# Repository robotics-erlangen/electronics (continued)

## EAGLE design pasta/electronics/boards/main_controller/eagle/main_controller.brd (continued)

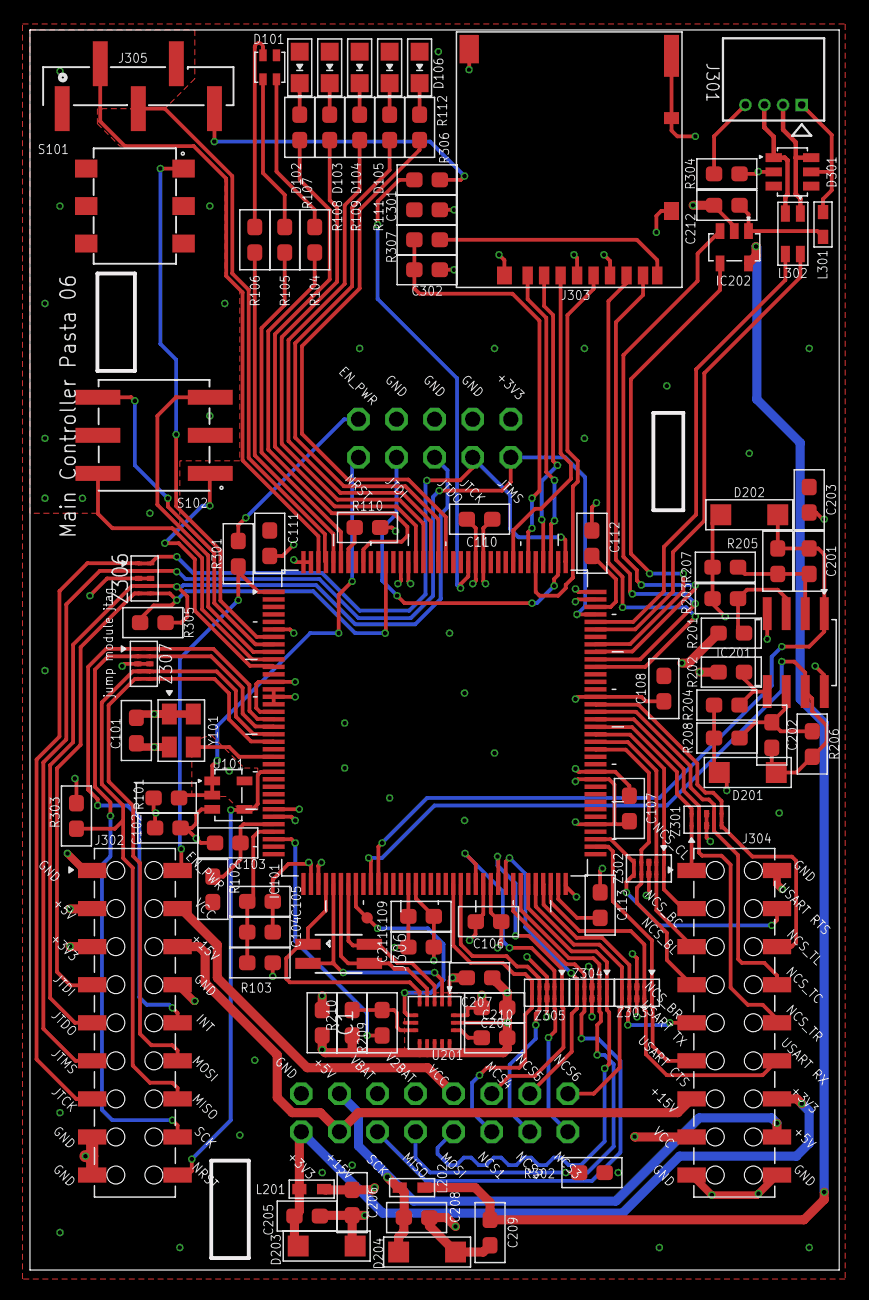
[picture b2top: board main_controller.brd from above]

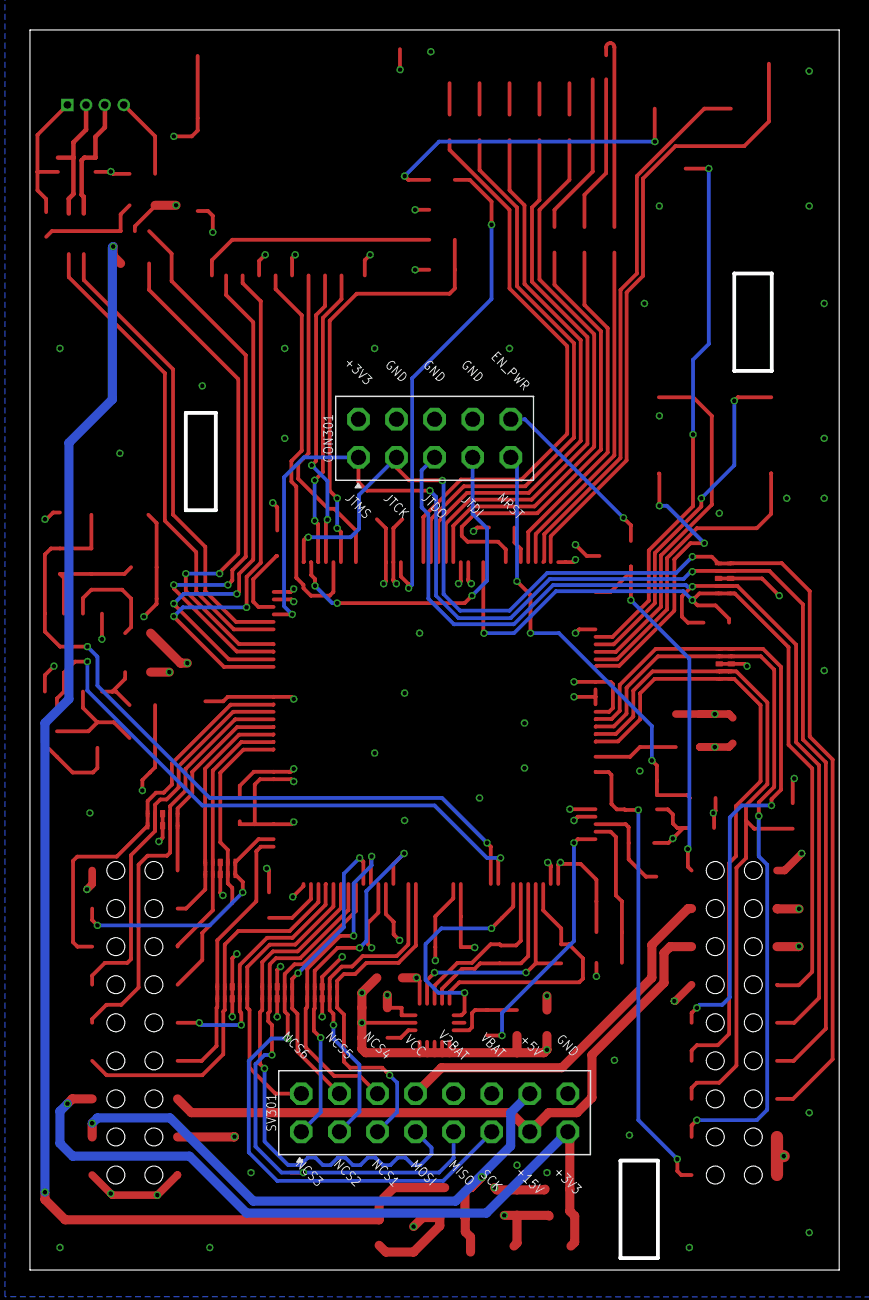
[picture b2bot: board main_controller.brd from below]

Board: 4 copper layers, 54.0 x 82.8 mm, 97 parts (2 on the bottom side), 104 nets.

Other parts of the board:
U$1: POWER_DISTRIBUTION_BOARD_TOP

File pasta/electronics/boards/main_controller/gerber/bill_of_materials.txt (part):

Stückliste exportiert aus D:/hardware/pasta/electronics/boards/main_controller/eagle/main_controller.sch am 04.07.2023 15:47

Part   Value             Device                     Package                  Description                                                                                                                          CAPACITANCE COPYRIGHT                                                DIELECTRIC FARNELL LINE1     LINE2    MF                          MOUSER               MPN              POPULARITY POWER RESISTANCE TOLERANCE VALUE             VOLTAGE WE-NUMBER              
301    TEST-POINT3       TEST-POINT3                PAD.03X.03                                                                                                                                                                                                                                                                                                                                                                                                                        
C1     100n ±10% 50V X7R C(100NF,50V,0603)          C0603                    Robotics Erlangen Capacitor Library                                                                                                  100n                                                                 X7R                100n ±10% 50V X7R  Würth Elektronik                                 885012206095                                 ±10%      100n ±10% 50V X7R 50V                            
C101   100n ±10% 50V X7R C(100NF,50V,0603)          C0603                    Robotics Erlangen Capacitor Library                                                                                                  100n                                                                 X7R                100n ±10% 50V X7R  Würth Elektronik                                 885012206095                                 ±10%      100n ±10% 50V X7R 50V                            
C102   100n ±10% 50V X7R C(100NF,50V,0603)          C0603                    Robotics Erlangen Capacitor Library                                                                                                  100n                                                                 X7R                100n ±10% 50V X7R  Würth Elektronik                                 885012206095                                 ±10%      100n ±10% 50V X7R 50V                            
C103   470n ±10% 25V X7R C(470NF,25V,0603)          C0603                    Robotics Erlangen Capacitor Library                                                                                                  470n                                                                 X7R                470n ±10% 25V X7R  Würth Elektronik                                 885012206075                                 ±10%      470n ±10% 25V X7R 25V                            
C104   1u ±10% 25V X7R   C(1.0UF,25V,0603)          C0603                    Robotics Erlangen Capacitor Library                                                                                                  1u                                                                   X7R                1u ±10%   25V X7R  Würth Elektronik                                 885012206076                                 ±10%      1u ±10% 25V X7R   25V                            
C105   100n ±10% 50V X7R C(100NF,50V,0603)          C0603                    Robotics Erlangen Capacitor Library                                                                                                  100n                                                                 X7R                100n ±10% 50V X7R  Würth Elektronik                                 885012206095                                 ±10%      100n ±10% 50V X7R 50V                            
C106   100n ±10% 50V X7R C(100NF,50V,0603)          C0603                    Robotics Erlangen Capacitor Library                                                                                                  100n                                                                 X7R                100n ±10% 50V X7R  Würth Elektronik                                 885012206095                                 ±10%      100n ±10% 50V X7R 50V                            
C107   100n ±10% 50V X7R C(100NF,50V,0603)          C0603                    Robotics Erlangen Capacitor Library                                                                                                  100n                                                                 X7R                100n ±10% 50V X7R  Würth Elektronik                                 885012206095                                 ±10%      100n ±10% 50V X7R 50V                            
C108   100n ±10% 50V X7R C(100NF,50V,0603)          C0603                    Robotics Erlangen Capacitor Library                                                                                                  100n                                                                 X7R                100n ±10% 50V X7R  Würth Elektronik                                 885012206095                                 ±10%      100n ±10% 50V X7R 50V                            
C109   100n ±10% 50V X7R C(100NF,50V,0603)          C0603                    Robotics Erlangen Capacitor Library                                                                                                  100n                                                                 X7R                100n ±10% 50V X7R  Würth Elektronik                                 885012206095                                 ±10%      100n ±10% 50V X7R 50V                            
C110   100n ±10% 50V X7R C(100NF,50V,0603)          C0603                    Robotics Erlangen Capacitor Library                                                                                                  100n                                                                 X7R                100n ±10% 50V X7R  Würth Elektronik                                 885012206095                                 ±10%      100n ±10% 50V X7R 50V                            
C111   4u7 ±20% 6V3 X5R  C(4.7UF,6.3V,0603)         C0603                    Robotics Erlangen Capacitor Library                                                                                                  4u7                                                                  X5R                4u7 ±20%  6V3 X5R  Würth Elektronik                                 885012106005                                 ±20%      4u7 ±20% 6V3 X5R  6V3                            
C112   2u2 ±20% 6V3 X5R  C(2.2UF,6.3V,0603)         C0603                    Robotics Erlangen Capacitor Library                                                                                                  2u2                                                                  X5R                2u2 ±20%  6V3 X5R  Würth Elektronik                                 885012106004                                 ±20%      2u2 ±20% 6V3 X5R  6V3                            
C113   2u2 ±20% 6V3 X5R  C(2.2UF,6.3V,0603)         C0603                    Robotics Erlangen Capacitor Library                                                                                                  2u2                                                                  X5R                2u2 ±20%  6V3 X5R  Würth Elektronik                                 885012106004                                 ±20%      2u2 ±20% 6V3 X5R  6V3                            
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
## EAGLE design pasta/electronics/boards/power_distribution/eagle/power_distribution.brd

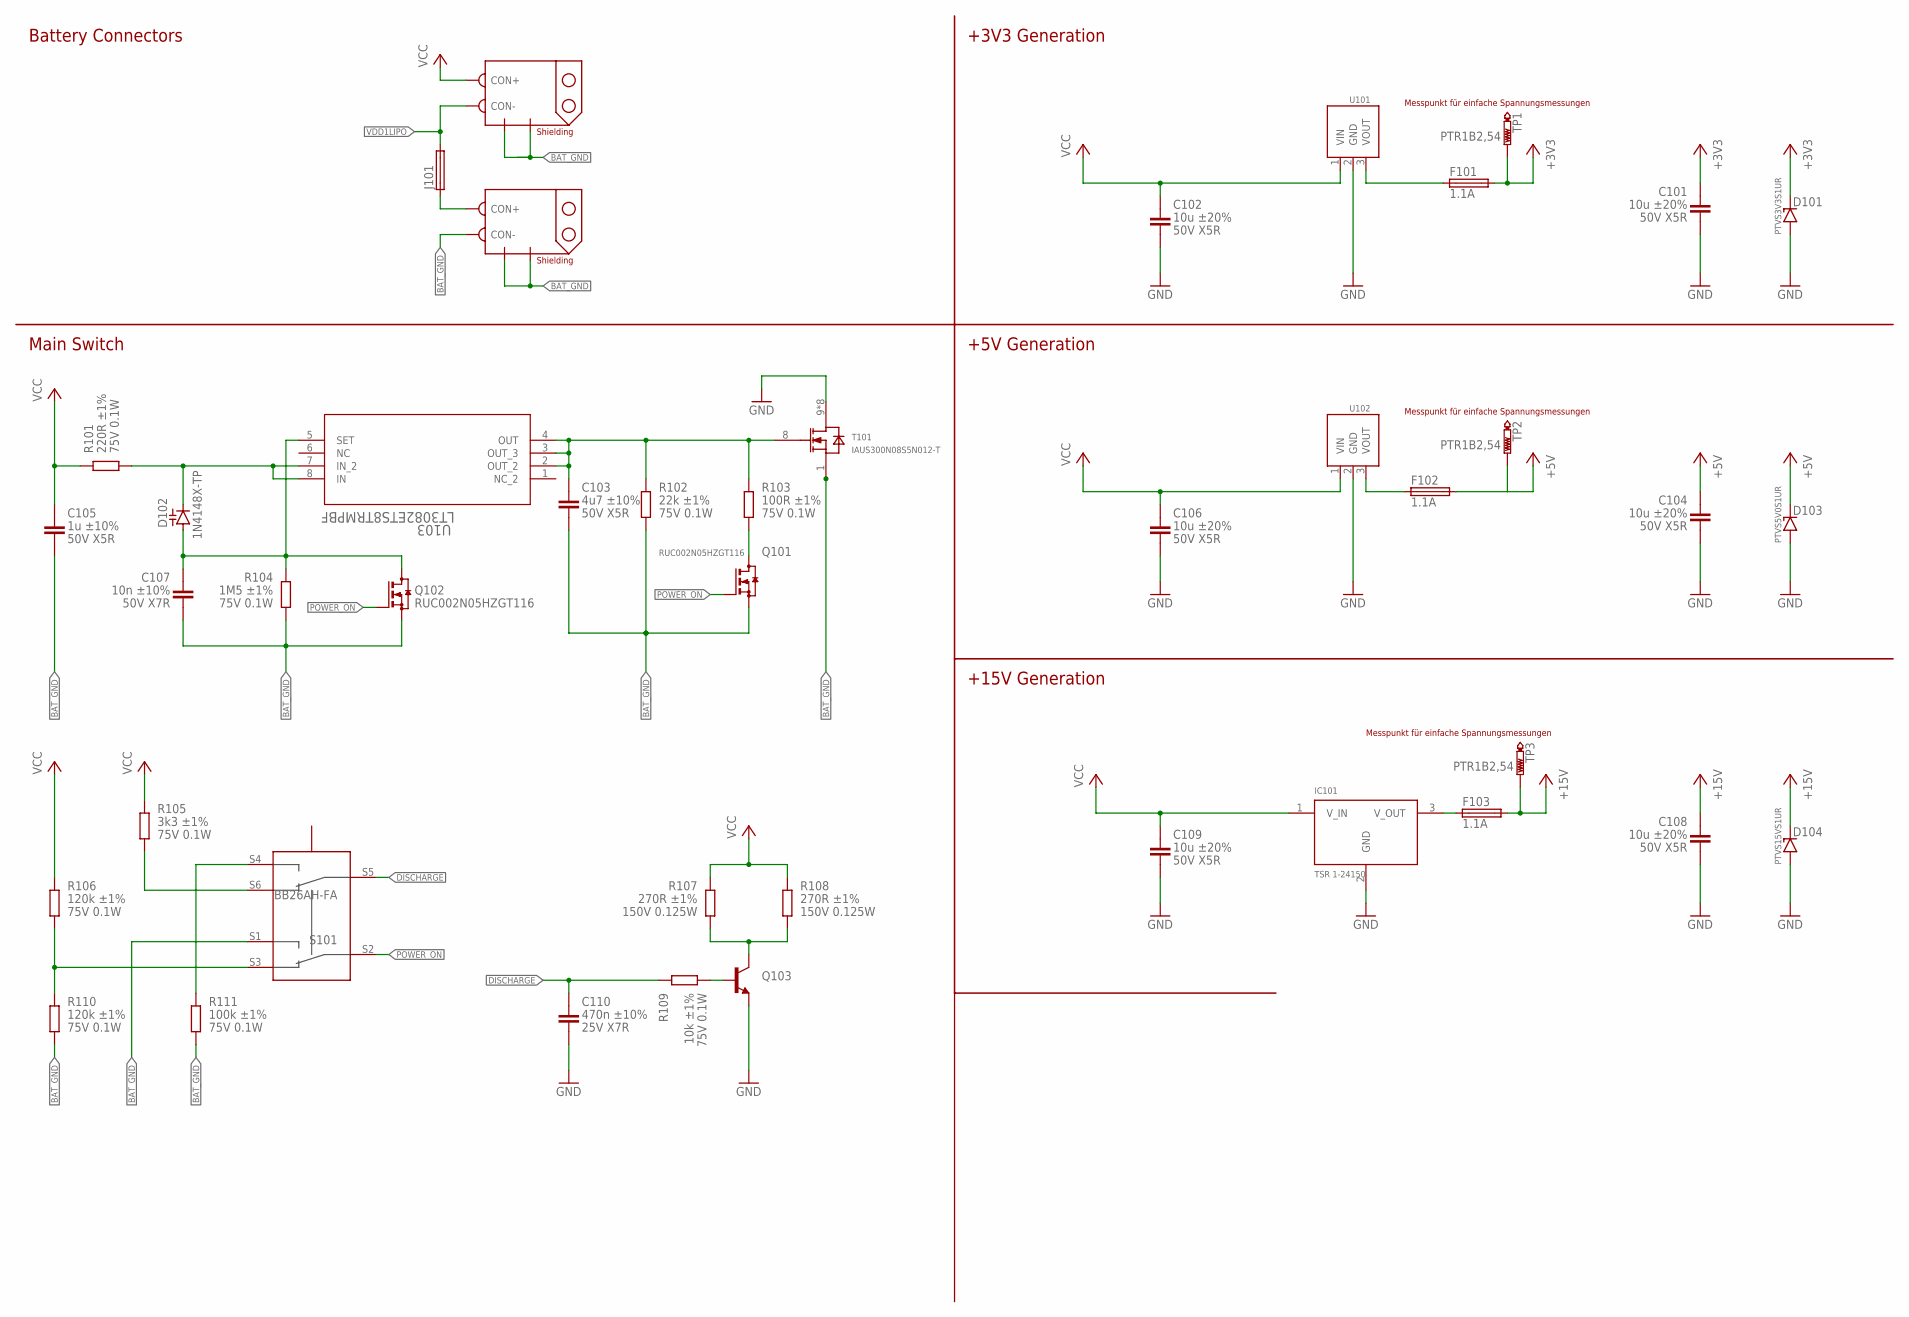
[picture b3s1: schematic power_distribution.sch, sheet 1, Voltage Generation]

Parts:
C101, C102, C104, C106, C108, C109: 10u ±20% 50V X5R; C1206
C103: 4u7 ±10% 50V X5R; C0805
C105: 1u ±10% 50V X5R; C0603
C107: 10n ±10% 50V X7R; C0603
C110: 470n ±10% 25V X7R; C0603
CON101, CON102: XT60PW; XT60PW-M
D101: PTVS3V3S1UR; SOD123
D102: 1N4148X-TP; SOD523
D103: PTVS5V0S1UR; SOD123
D104: PTVS15VS1UR; SOD123
F101, F102, F103: 1.1A; MF-NSMF-1
IC101: TSR 1-24150; TRACO_POWER_3_PIN
J101: 696107003002
Q101, Q102: RUC002N05HZGT116; SOT23
Q103: FJT44TF"; SOT223
R101: 220R ±1% 75V 0.1W; R0603
R102: 22k ±1% 75V 0.1W; R0603
R103: 100R ±1% 75V 0.1W; R0603
R104: 1M5 ±1% 75V 0.1W; R0603
R105: 3k3 ±1% 75V 0.1W; R0603
R106, R110: 120k ±1% 75V 0.1W; R0603
R107, R108: 270R ±1% 150V 0.125W; R0805
R109: 10k ±1% 75V 0.1W; R0603
R111: 100k ±1% 75V 0.1W; R0603
S101: BB26AH-FA; BB26AH
T101: IAUS300N08S5N012-T; SOIC120P1500X235-16N-1-V
TP1, TP2, TP3: PTR1B2,54; B2,54
U101: FDSM_SIP-3_173010342; FDSM-173XXXX42
U102: FDSM_SIP-3_173010542; FDSM-173XXXX42
U103: LT3082ETS8TRMPBF; TSOT-23_TS8

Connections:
+3V3: C101.1, D101.C (KATHODE), F101.2, TP1.TP; also elsewhere on the board
+5V: C104.1, D103.C (KATHODE), F102.2, TP2.TP; also elsewhere on the board
+15V: C108.1, D104.C (KATHODE), F103.2, TP3.TP; also elsewhere on the board
BAT_GND: C103.2, C105.2, C107.2, CON101.S1, CON101.S2, CON102.CON-, CON102.S1, CON102.S2, Q101.2 (S), Q102.2 (S), R102.1, R104.1, R110.1, R111.1, S101.S1 (2), T101.1 (SOURCE_1)
DISCHARGE: C110.1, R109.1, S101.S5 (4)
GND: C101.2, C102.2, C104.2, C106.2, C108.2, C109.2, C110.2, D101.A (ANODE), D103.A (ANODE), D104.A (ANODE), IC101.2 (GND), Q103.3 (E), T101.9 (DRAIN), T101.10 (DRAIN), T101.11 (DRAIN), T101.12 (DRAIN), T101.13 (DRAIN), T101.14 (DRAIN), T101.15 (DRAIN), T101.16 (DRAIN), U101.2 (GND), U102.2 (GND); also elsewhere on the board
unnamed: CON102.CON+, J101.1
unnamed: C103.1, R102.2, R103.2, T101.8 (GATE), U103.2 (OUT_2), U103.3 (OUT_3), U103.4 (OUT)
unnamed: Q101.3 (D), R103.1
unnamed: R106.1, R110.2, S101.S3 (3)
unnamed: F101.1, U101.3 (VOUT)
unnamed: R105.1, S101.S6 (6)
unnamed: F103.1, IC101.3 (V_OUT)
unnamed: R111.2, S101.S4 (5)
unnamed: F102.1, U102.3 (VOUT)
unnamed: Q103.2 (C), Q103.4 (C), R107.1, R108.1
unnamed: Q103.1 (B), R109.2
unnamed: D102.C, R101.1, U103.7 (IN_2), U103.8 (IN)
POWER_ON: Q101.1 (G), Q102.1 (G), S101.S2 (1)
SETPIN: C107.1, D102.A, Q102.3 (D), R104.2, U103.5 (SET)
VCC: C102.1, C105.1, C106.1, C109.1, CON101.CON+, IC101.1 (V_IN), R101.2, R105.2, R106.2, R107.2, R108.2, U101.1 (VIN), U102.1 (VIN); also elsewhere on the board
VDD1LIPO: CON101.CON-, J101.2; also elsewhere on the board

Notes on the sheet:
+3V3 Generation
+5V Generation
+15V Generation
Main Switch
Battery Connectors
Messpunkt für einfache Spannungsmessungen

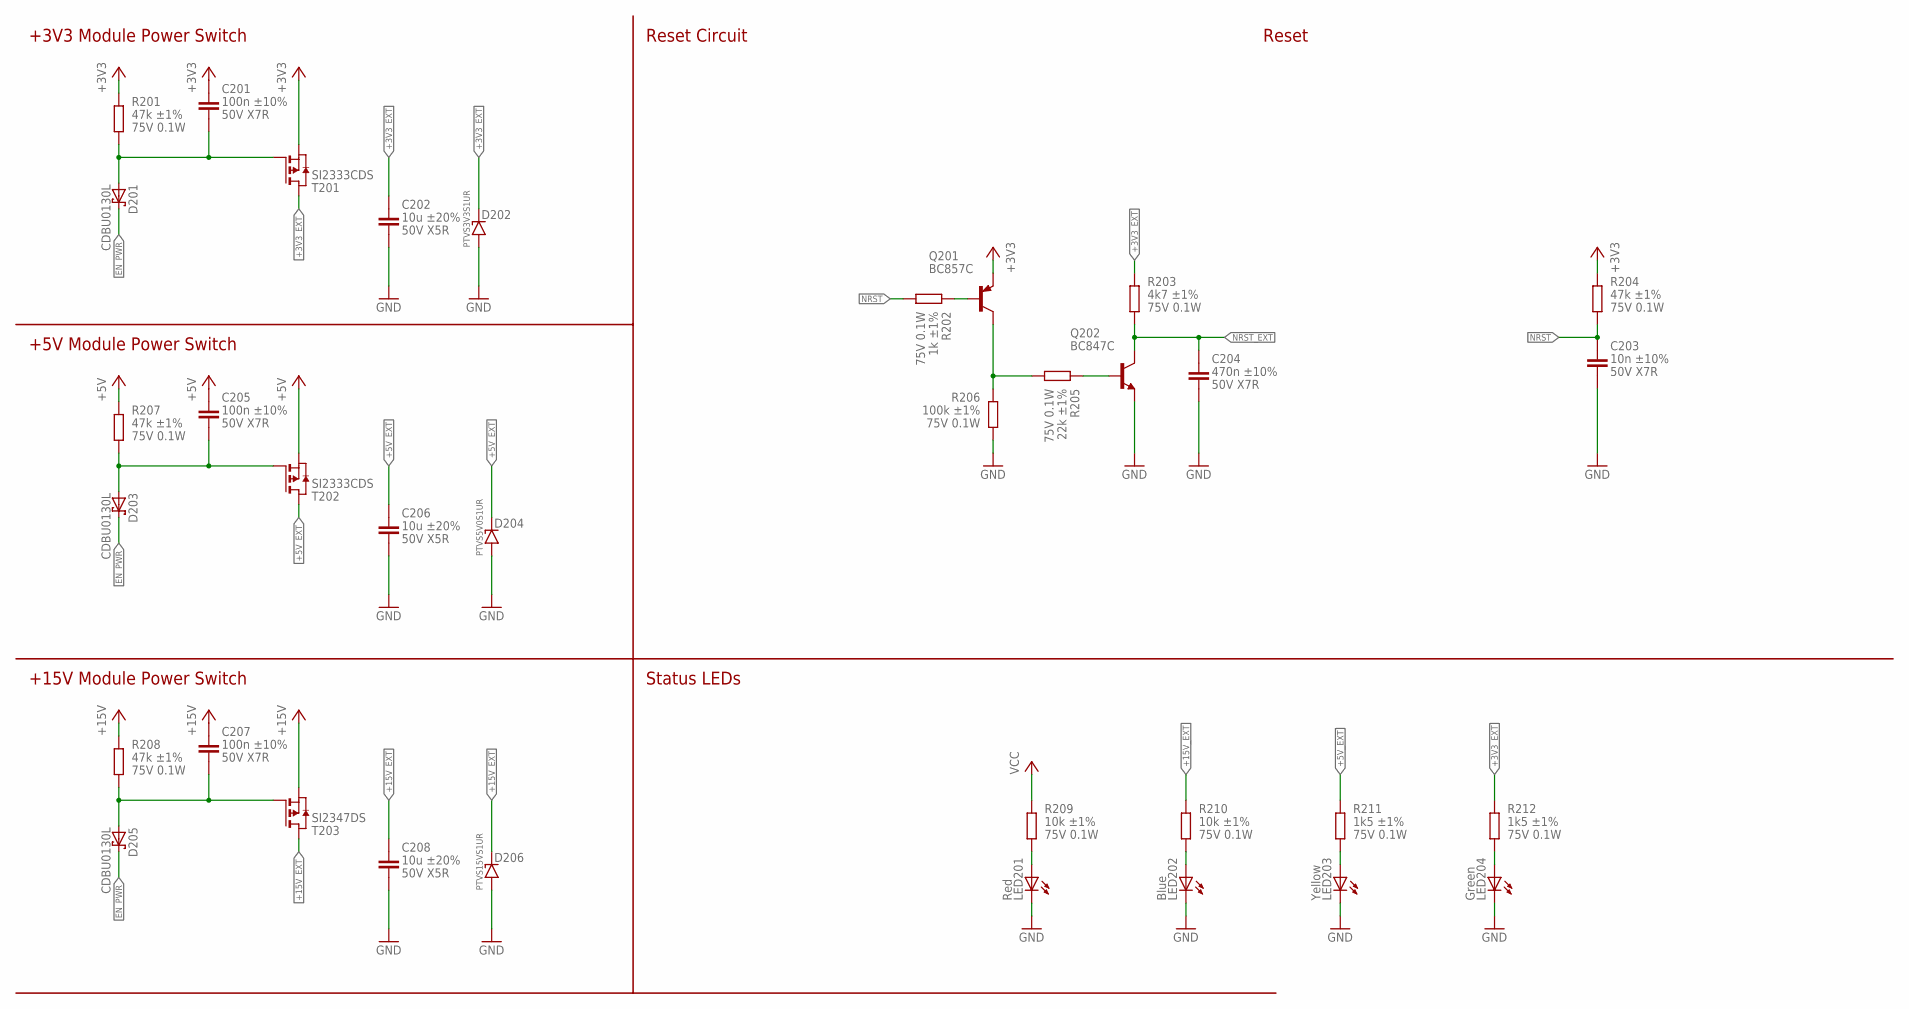
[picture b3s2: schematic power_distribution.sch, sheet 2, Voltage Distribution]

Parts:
C201, C205, C207: 100n ±10% 50V X7R; C0603
C202, C206, C208: 10u ±20% 50V X5R; C1206
C203: 10n ±10% 50V X7R; C0603
C204: 470n ±10% 50V X7R; C0603
D201, D203, D205: CDBU0130L; 0603
D202: PTVS3V3S1UR; SOD123
D204: PTVS5V0S1UR; SOD123
D206: PTVS15VS1UR; SOD123
LED201: Red; CHIPLED_0805
LED202: Blue; CHIPLED_0805
LED203: Yellow; CHIPLED_0805
LED204: Green; CHIPLED_0805
Q201: BC857C; SOT23-BEC; MPN BC857CW,115; MOUSER 771-BC857CW115
Q202: BC847C; SOT23; MPN BC847CW,115; MOUSER 771-BC847CW-T/R
R201, R204, R207, R208: 47k ±1% 75V 0.1W; R0603
R202: 1k ±1% 75V 0.1W; R0603
R203: 4k7 ±1% 75V 0.1W; R0603
R205: 22k ±1% 75V 0.1W; R0603
R206: 100k ±1% 75V 0.1W; R0603
R209, R210: 10k ±1% 75V 0.1W; R0603
R211, R212: 1k5 ±1% 75V 0.1W; R0603
T201, T202: SI2333CDS; SOT23
T203: SI2347DS; SOT23

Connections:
+3V3: C201.1, Q201.E, R201.2, R204.2, T201.2 (S); also elsewhere on the board
+3V3_EXT: C202.1, D202.C (KATHODE), R203.2, R212.2, T201.3 (D); also elsewhere on the board
+5V: C205.1, R207.2, T202.2 (S); also elsewhere on the board
+5V_EXT: C206.1, D204.C (KATHODE), R211.2, T202.3 (D); also elsewhere on the board
+15V: C207.1, R208.2, T203.2 (S); also elsewhere on the board
+15V_EXT: C208.1, D206.C (KATHODE), R210.2, T203.3 (D); also elsewhere on the board
EN_PWR: D201.2 (C), D203.2 (C), D205.2 (C); also elsewhere on the board
GND: C202.2, C203.2, C204.2, C206.2, C208.2, D202.A (ANODE), D204.A (ANODE), D206.A (ANODE), LED201.C, LED202.C, LED203.C, LED204.C, Q202.2 (E), R206.1; also elsewhere on the board
unnamed: LED201.A, R209.1
unnamed: C201.2, D201.1 (A), R201.1, T201.1 (G)
unnamed: C205.2, D203.1 (A), R207.1, T202.1 (G)
unnamed: C207.2, D205.1 (A), R208.1, T203.1 (G)
unnamed: LED204.A, R212.1
unnamed: LED203.A, R211.1
unnamed: Q201.B, R202.2
unnamed: Q201.C, R205.1, R206.2
unnamed: Q202.1 (B), R205.2
unnamed: LED202.A, R210.1
NRST: C203.1, R202.1, R204.1; also elsewhere on the board
NRST_EXT: C204.1, Q202.3 (C), R203.1; also elsewhere on the board
VCC: R209.2; also elsewhere on the board

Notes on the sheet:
+3V3 Module Power Switch
+5V Module Power Switch
+15V Module Power Switch
Status LEDs
Reset Circuit
Reset

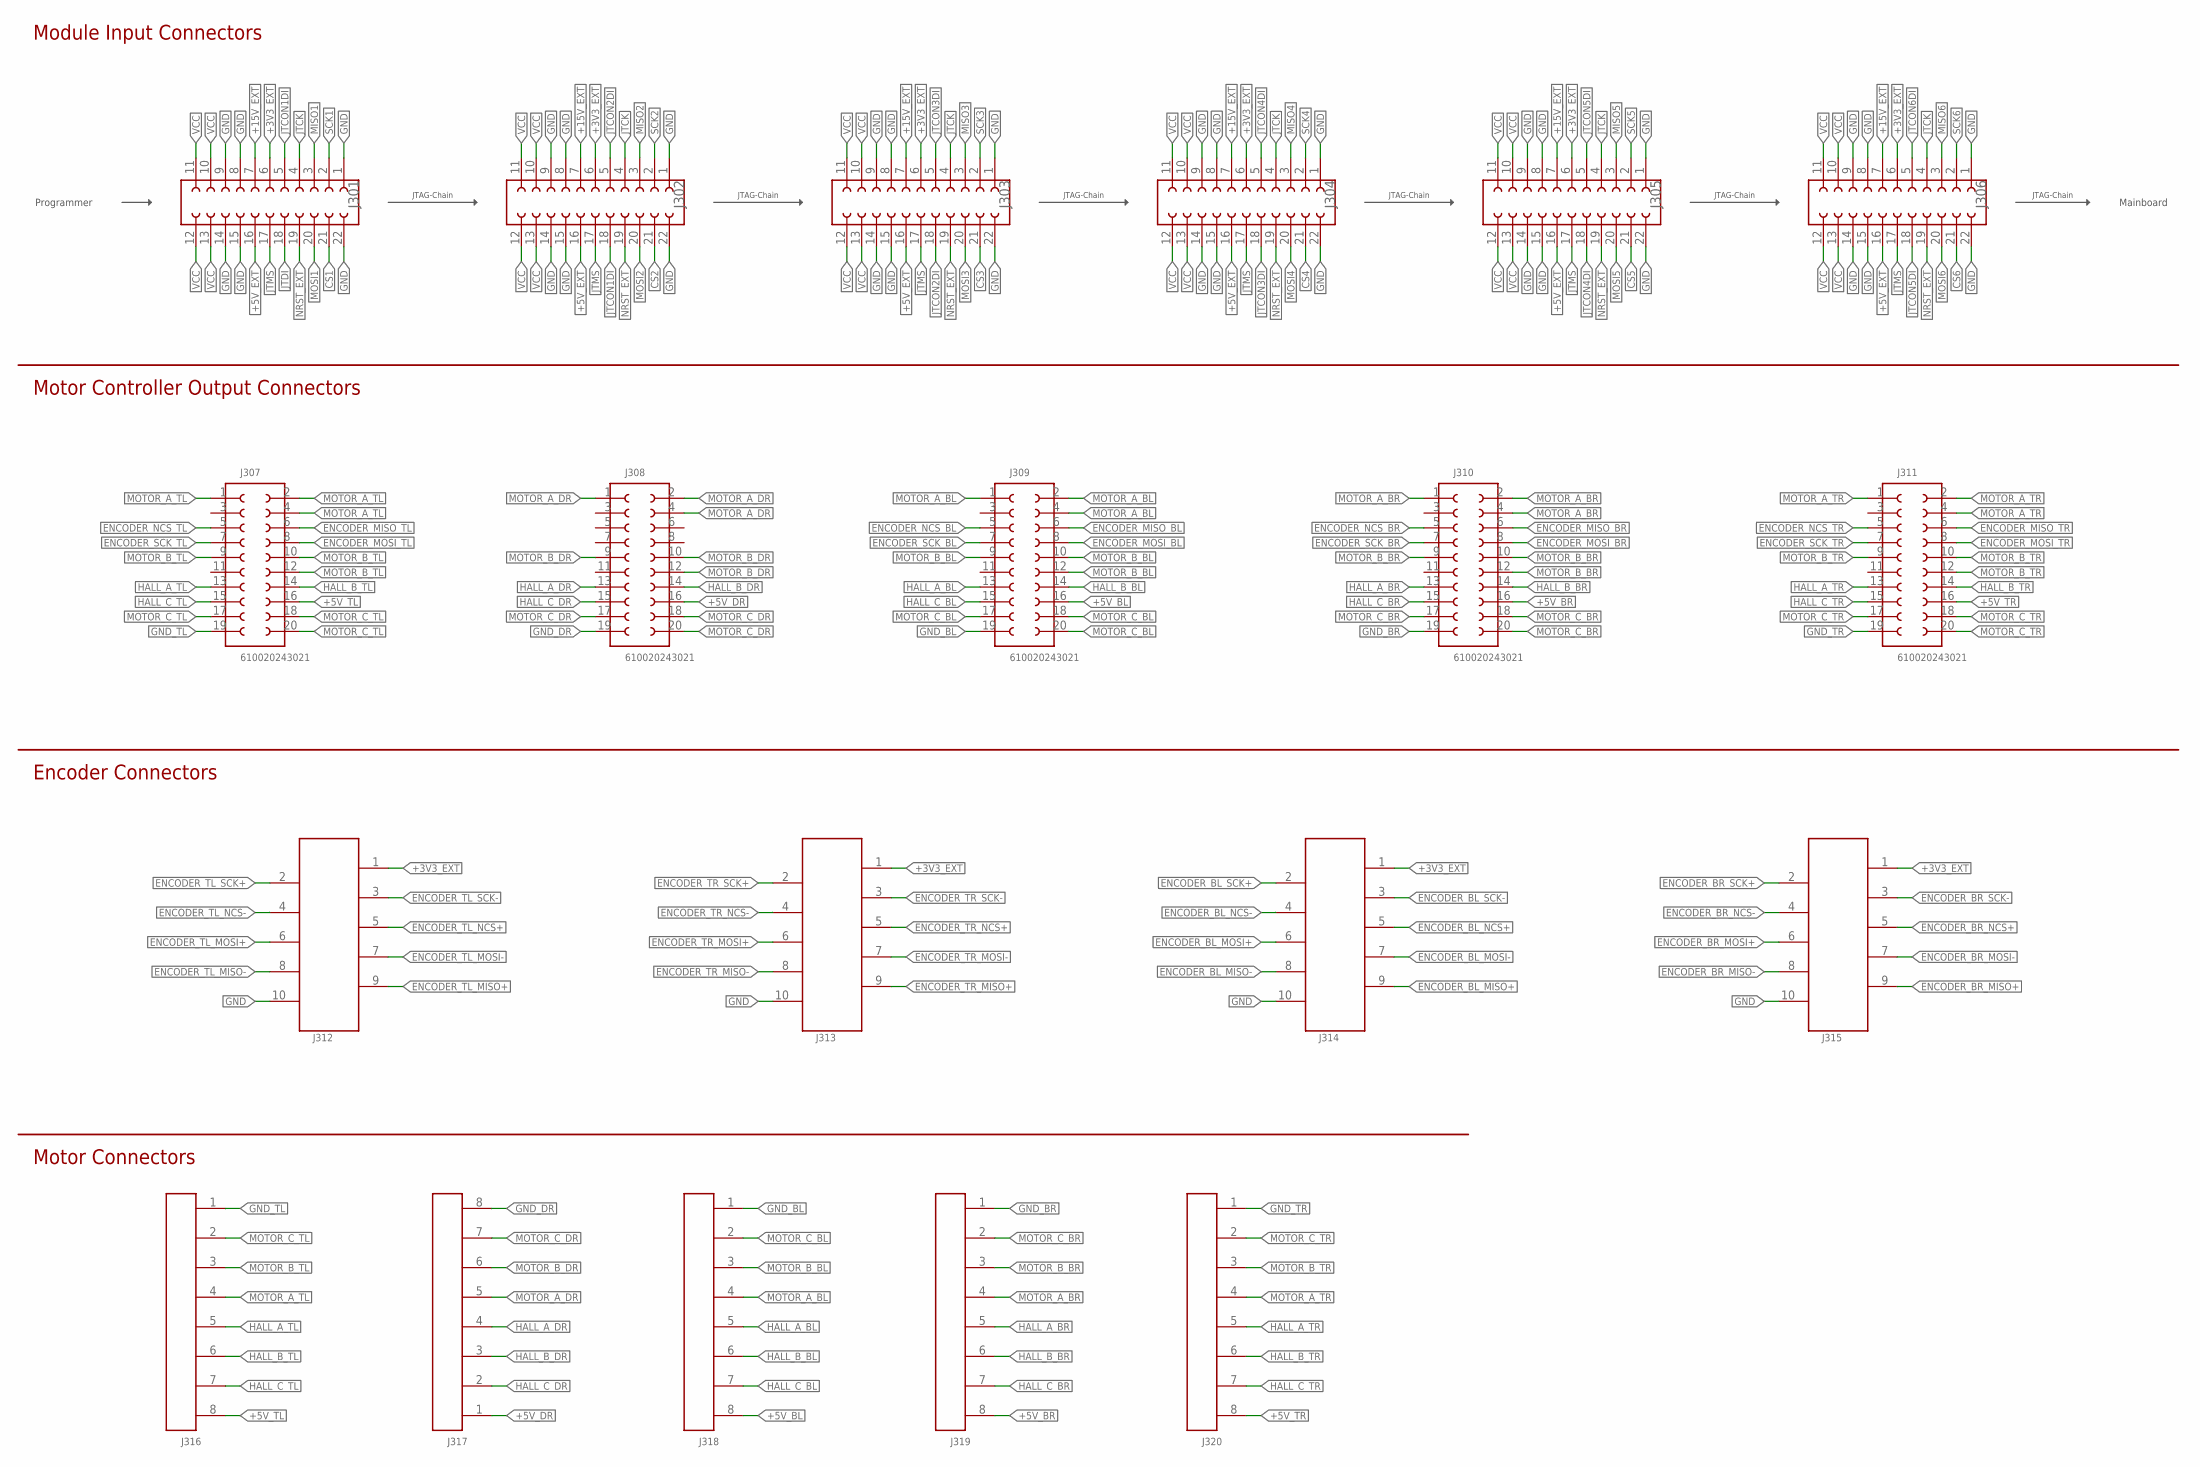
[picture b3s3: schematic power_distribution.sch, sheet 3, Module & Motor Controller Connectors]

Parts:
J301, J302, J303, J304, J305, J306: 610022243021
J307, J308, J309, J310, J311: 610020243021; 610X20243021
J312, J313, J314, J315: 690368171072
J316, J318, J319, J320: 66100811622
J317: 66100811722

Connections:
+3V3_EXT: J301.6, J302.6, J303.6, J304.6, J305.6, J306.6, J312.1 (10), J313.1 (10), J314.1 (10), J315.1 (10); also elsewhere on the board
+5V_BL: J309.16 (8), J318.8
+5V_BR: J310.16 (8), J319.8
+5V_DR: J308.16 (8), J317.1 (8)
+5V_EXT: J301.16, J302.16, J303.16, J304.16, J305.16, J306.16; also elsewhere on the board
+5V_TL: J307.16 (8), J316.8
+5V_TR: J311.16 (8), J320.8
+15V_EXT: J301.7, J302.7, J303.7, J304.7, J305.7, J306.7; also elsewhere on the board
CS1: J301.21; also elsewhere on the board
CS2: J302.21; also elsewhere on the board
CS3: J303.21; also elsewhere on the board
CS4: J304.21; also elsewhere on the board
CS5: J305.21; also elsewhere on the board
CS6: J306.21; also elsewhere on the board
ENCODER_BL_MISO+: J314.9 (2); also elsewhere on the board
ENCODER_BL_MISO-: J314.8 (3); also elsewhere on the board
ENCODER_BL_MOSI+: J314.6 (5); also elsewhere on the board
ENCODER_BL_MOSI-: J314.7 (4); also elsewhere on the board
ENCODER_BL_NCS+: J314.5 (6); also elsewhere on the board
ENCODER_BL_NCS-: J314.4 (7); also elsewhere on the board
ENCODER_BL_SCK+: J314.2 (9); also elsewhere on the board
ENCODER_BL_SCK-: J314.3 (8); also elsewhere on the board
ENCODER_BR_MISO+: J315.9 (2); also elsewhere on the board
ENCODER_BR_MISO-: J315.8 (3); also elsewhere on the board
ENCODER_BR_MOSI+: J315.6 (5); also elsewhere on the board
ENCODER_BR_MOSI-: J315.7 (4); also elsewhere on the board
ENCODER_BR_NCS+: J315.5 (6); also elsewhere on the board
ENCODER_BR_NCS-: J315.4 (7); also elsewhere on the board
ENCODER_BR_SCK+: J315.2 (9); also elsewhere on the board
ENCODER_BR_SCK-: J315.3 (8); also elsewhere on the board
ENCODER_MISO_BL: J309.6 (3); also elsewhere on the board
ENCODER_MISO_BR: J310.6 (3); also elsewhere on the board
ENCODER_MISO_TL: J307.6 (3); also elsewhere on the board
ENCODER_MISO_TR: J311.6 (3); also elsewhere on the board
ENCODER_MOSI_BL: J309.8 (4); also elsewhere on the board
ENCODER_MOSI_BR: J310.8 (4); also elsewhere on the board
ENCODER_MOSI_TL: J307.8 (4); also elsewhere on the board
ENCODER_MOSI_TR: J311.8 (4); also elsewhere on the board
ENCODER_NCS_BL: J309.5 (18); also elsewhere on the board
ENCODER_NCS_BR: J310.5 (18); also elsewhere on the board
ENCODER_NCS_TL: J307.5 (18); also elsewhere on the board
ENCODER_NCS_TR: J311.5 (18); also elsewhere on the board
ENCODER_SCK_BL: J309.7 (17); also elsewhere on the board
ENCODER_SCK_BR: J310.7 (17); also elsewhere on the board
ENCODER_SCK_TL: J307.7 (17); also elsewhere on the board
ENCODER_SCK_TR: J311.7 (17); also elsewhere on the board
ENCODER_TL_MISO+: J312.9 (2); also elsewhere on the board
ENCODER_TL_MISO-: J312.8 (3); also elsewhere on the board
ENCODER_TL_MOSI+: J312.6 (5); also elsewhere on the board
ENCODER_TL_MOSI-: J312.7 (4); also elsewhere on the board
ENCODER_TL_NCS+: J312.5 (6); also elsewhere on the board
ENCODER_TL_NCS-: J312.4 (7); also elsewhere on the board
ENCODER_TL_SCK+: J312.2 (9); also elsewhere on the board
ENCODER_TL_SCK-: J312.3 (8); also elsewhere on the board
ENCODER_TR_MISO+: J313.9 (2); also elsewhere on the board
ENCODER_TR_MISO-: J313.8 (3); also elsewhere on the board
ENCODER_TR_MOSI+: J313.6 (5); also elsewhere on the board
ENCODER_TR_MOSI-: J313.7 (4); also elsewhere on the board
ENCODER_TR_NCS+: J313.5 (6); also elsewhere on the board
ENCODER_TR_NCS-: J313.4 (7); also elsewhere on the board
ENCODER_TR_SCK+: J313.2 (9); also elsewhere on the board
ENCODER_TR_SCK-: J313.3 (8); also elsewhere on the board
GND: J301.1, J301.8, J301.9, J301.14, J301.15, J301.22, J302.1, J302.8, J302.9, J302.14, J302.15, J302.22, J303.1, J303.8, J303.9, J303.14, J303.15, J303.22, J304.1, J304.8, J304.9, J304.14, J304.15, J304.22, J305.1, J305.8, J305.9, J305.14, J305.15, J305.22, J306.1, J306.8, J306.9, J306.14, J306.15, J306.22, J312.10 (1), J313.10 (1), J314.10 (1), J315.10 (1); also elsewhere on the board
GND_BL: J309.19 (11), J318.1
GND_BR: J310.19 (11), J319.1
GND_DR: J308.19 (11), J317.8 (1)
GND_TL: J307.19 (11), J316.1
GND_TR: J311.19 (11), J320.1
HALL_A_BL: J309.13 (14), J318.5
HALL_A_BR: J310.13 (14), J319.5
HALL_A_DR: J308.13 (14), J317.4 (5)
HALL_A_TL: J307.13 (14), J316.5
HALL_A_TR: J311.13 (14), J320.5
HALL_B_BL: J309.14 (7), J318.6
HALL_B_BR: J310.14 (7), J319.6
HALL_B_DR: J308.14 (7), J317.3 (6)
HALL_B_TL: J307.14 (7), J316.6
HALL_B_TR: J311.14 (7), J320.6
HALL_C_BL: J309.15 (13), J318.7
HALL_C_BR: J310.15 (13), J319.7
HALL_C_DR: J308.15 (13), J317.2 (7)
HALL_C_TL: J307.15 (13), J316.7
HALL_C_TR: J311.15 (13), J320.7
JTCK: J301.4, J302.4, J303.4, J304.4, J305.4, J306.4; also elsewhere on the board
JTCON1DI: J301.5, J302.18; also elsewhere on the board
JTCON2DI: J302.5, J303.18; also elsewhere on the board
JTCON3DI: J303.5, J304.18; also elsewhere on the board
JTCON4DI: J304.5, J305.18; also elsewhere on the board
JTCON5DI: J305.5, J306.18; also elsewhere on the board
JTCON6DI: J306.5; also elsewhere on the board
JTDI: J301.18; also elsewhere on the board
JTMS: J301.17, J302.17, J303.17, J304.17, J305.17, J306.17; also elsewhere on the board
MISO1: J301.3; also elsewhere on the board
MISO2: J302.3; also elsewhere on the board
MISO3: J303.3; also elsewhere on the board
MISO4: J304.3; also elsewhere on the board
MISO5: J305.3; also elsewhere on the board
MISO6: J306.3; also elsewhere on the board
MOSI1: J301.20; also elsewhere on the board
MOSI2: J302.20; also elsewhere on the board
MOSI3: J303.20; also elsewhere on the board
MOSI4: J304.20; also elsewhere on the board
MOSI5: J305.20; also elsewhere on the board
MOSI6: J306.20; also elsewhere on the board
MOTOR_A_BL: J309.1 (20), J309.2 (1), J309.4 (2), J318.4
MOTOR_A_BR: J310.1 (20), J310.2 (1), J310.4 (2), J319.4
MOTOR_A_DR: J308.1 (20), J308.2 (1), J308.4 (2), J317.5 (4)
MOTOR_A_TL: J307.1 (20), J307.2 (1), J307.4 (2), J316.4
MOTOR_A_TR: J311.1 (20), J311.2 (1), J311.4 (2), J320.4
MOTOR_B_BL: J309.9 (16), J309.10 (5), J309.12 (6), J318.3
MOTOR_B_BR: J310.9 (16), J310.10 (5), J310.12 (6), J319.3
MOTOR_B_DR: J308.9 (16), J308.10 (5), J308.12 (6), J317.6 (3)
MOTOR_B_TL: J307.9 (16), J307.10 (5), J307.12 (6), J316.3
MOTOR_B_TR: J311.9 (16), J311.10 (5), J311.12 (6), J320.3
MOTOR_C_BL: J309.17 (12), J309.18 (9), J309.20 (10), J318.2
MOTOR_C_BR: J310.17 (12), J310.18 (9), J310.20 (10), J319.2
MOTOR_C_DR: J308.17 (12), J308.18 (9), J308.20 (10), J317.7 (2)
MOTOR_C_TL: J307.17 (12), J307.18 (9), J307.20 (10), J316.2
MOTOR_C_TR: J311.17 (12), J311.18 (9), J311.20 (10), J320.2
NRST_EXT: J301.19, J302.19, J303.19, J304.19, J305.19, J306.19; also elsewhere on the board
SCK1: J301.2; also elsewhere on the board
SCK2: J302.2; also elsewhere on the board
SCK3: J303.2; also elsewhere on the board
SCK4: J304.2; also elsewhere on the board
SCK5: J305.2; also elsewhere on the board
SCK6: J306.2; also elsewhere on the board
VCC: J301.10, J301.11, J301.12, J301.13, J302.10, J302.11, J302.12, J302.13, J303.10, J303.11, J303.12, J303.13, J304.10, J304.11, J304.12, J304.13, J305.10, J305.11, J305.12, J305.13, J306.10, J306.11, J306.12, J306.13; also elsewhere on the board

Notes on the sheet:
Module Input Connectors
JTAG-Chain
Mainboard
Programmer
Motor Controller Output Connectors
Encoder Connectors
Motor Connectors
